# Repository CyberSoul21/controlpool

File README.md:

# controlpool
Year: May - 2019
Controller for pool system for eliminate offensive Chemical Odors, Handling Chemicals, and Damage To Pool Equipment.

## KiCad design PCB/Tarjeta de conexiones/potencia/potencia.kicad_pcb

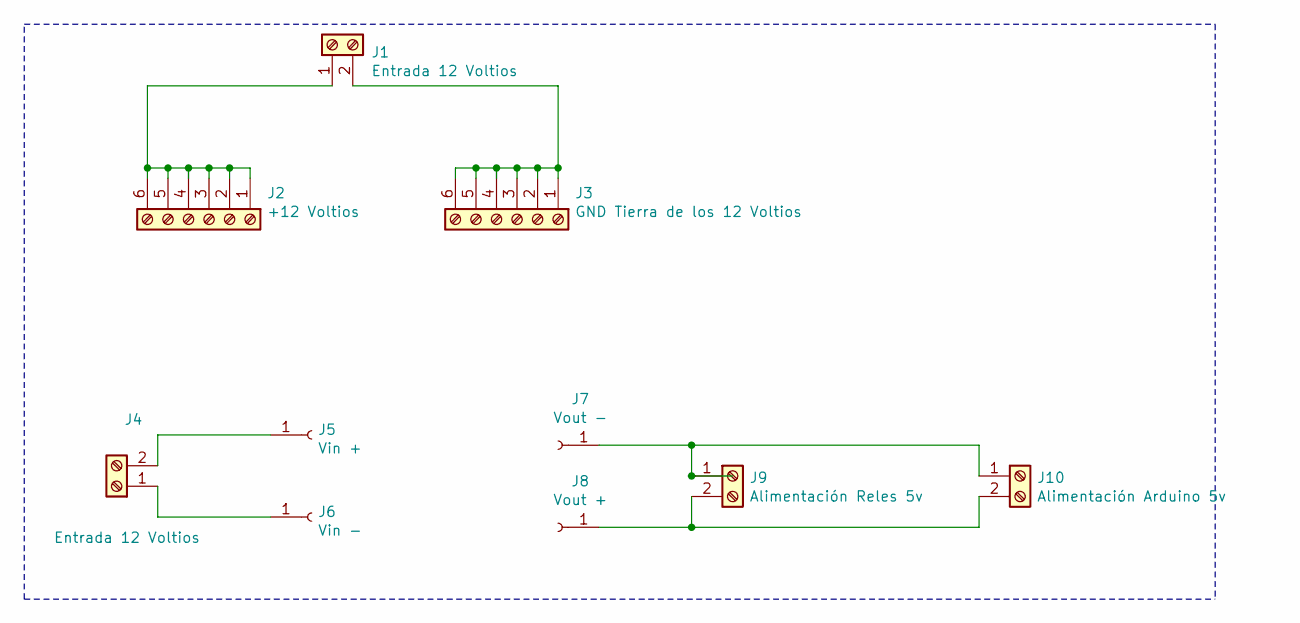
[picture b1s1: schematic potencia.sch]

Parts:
J1, J4: Entrada 12 Voltios; Altech_AK300_1x02_P5.00mm_45-Degree
J2: +12 Voltios; Altech_AK300_1x06_P5.00mm_45-Degree
J3: GND Tierra de los 12 Voltios; Altech_AK300_1x06_P5.00mm_45-Degree
J5: Vin +; PinSocket_1x01_P2.54mm_Vertical
J6: Vin -; PinSocket_1x01_P2.54mm_Vertical
J7: Vout -; PinSocket_1x01_P2.54mm_Vertical
J8: Vout +; PinSocket_1x01_P2.54mm_Vertical
J9: Alimentación Reles 5v; Altech_AK300_1x02_P5.00mm_45-Degree
J10: Alimentación Arduino 5v; Altech_AK300_1x02_P5.00mm_45-Degree

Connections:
unnamed: J1.1, J2.1, J2.2, J2.3, J2.4, J2.5, J2.6
unnamed: J1.2, J3.1, J3.2, J3.3, J3.4, J3.5, J3.6
unnamed: J4.1, J6.1
unnamed: J4.2, J5.1
unnamed: J7.1, J9.1, J10.1
unnamed: J8.1, J9.2, J10.2

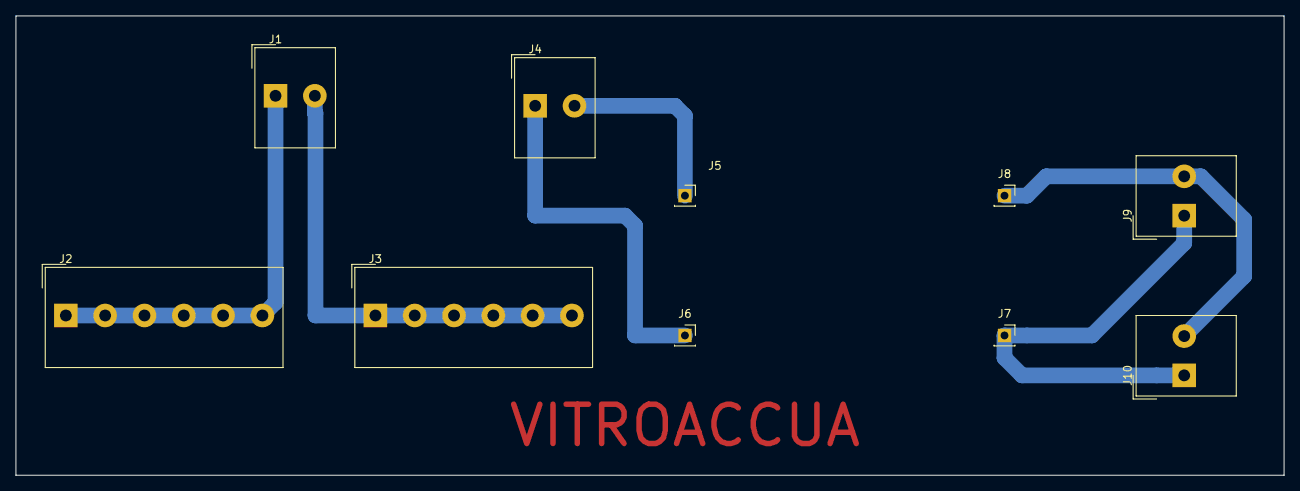
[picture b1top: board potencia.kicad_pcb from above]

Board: 2 copper layers, 161.3 x 58.4 mm, 10 parts (0 on the bottom side), 6 nets.

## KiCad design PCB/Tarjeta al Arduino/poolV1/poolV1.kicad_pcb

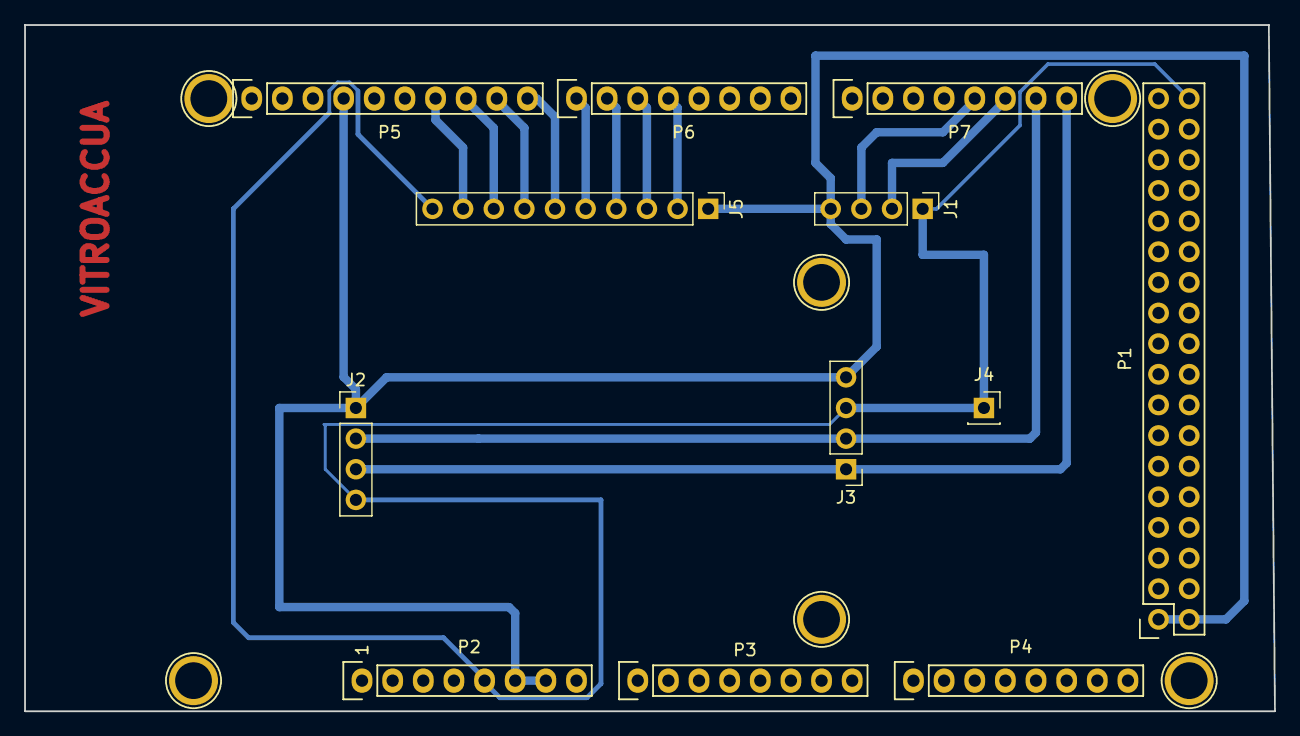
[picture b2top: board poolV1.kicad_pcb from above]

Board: 2 copper layers, 103.6 x 56.9 mm, 18 parts (0 on the bottom side), 14 nets.

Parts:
J1: LCD; PinHeader_1x04_P2.54mm_Vertical
J2: MEMORIA; PinHeader_1x04_P2.54mm_Vertical
J3: RTC; PinHeader_1x04_P2.54mm_Vertical
J4: 5 voltios; PinSocket_1x01_P2.54mm_Vertical
J5: RELES; PinHeader_1x10_P2.54mm_Vertical
P1: Digital; Socket_Strip_Arduino_2x18
P2: Power; Socket_Strip_Arduino_1x08
P3, P4: Analog; Socket_Strip_Arduino_1x08
P5: PWM; Socket_Strip_Arduino_1x10
P6: PWM; Socket_Strip_Arduino_1x08
P7: Communication; Socket_Strip_Arduino_1x08
P8, P9, P10, P11, P12, P13: CONN_01X01; Arduino_1pin

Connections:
+5V: J1.1, J2.4, J3.3, J4.1, J5.10, P1.35, P1.36, P2.5
/4(**): J5.2, P6.4
/5(**): J5.3, P6.3
/6(**): J5.4, P6.2
/7(**): J5.5, P6.1
/8(**): J5.6, P5.10
/9(**): J5.7, P5.9
/10(**): J5.8, P5.8
/11(**): J5.9, P5.7
/18(Tx1): J1.3, P7.5
/19(Rx1): J1.2, P7.6
/20(SDA): J2.2, J3.2, P7.7
/21(SCL): J2.3, J3.1, P7.8
GND: J1.4, J2.1, J3.4, J5.1, P1.1, P1.2, P2.6, P2.7, P5.4
